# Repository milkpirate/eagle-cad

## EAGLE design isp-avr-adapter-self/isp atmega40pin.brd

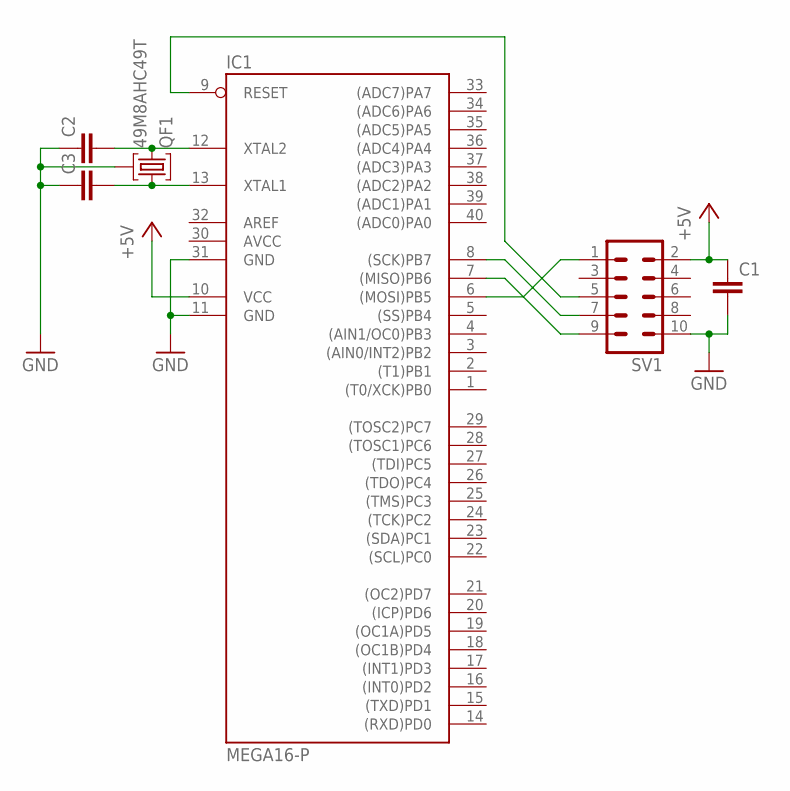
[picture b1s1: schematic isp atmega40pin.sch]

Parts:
C1, C2, C3: C-EU025-025X050; C025-025X050
IC1: MEGA16-P; DIL40
QF1: 49M8AHC49T; HC49U
SV1: ML10

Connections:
+5V: C1.1, IC1.10 (VCC), SV1.2
AVCC: IC1.30 (AVCC)
GND: C1.2, C2.1, C3.1, IC1.11 (GND), IC1.31 (GND), QF1.2, SV1.10
unnamed: IC1.6 ((MOSI)PB5), SV1.1
unnamed: C2.2, IC1.12 (XTAL2), QF1.3
unnamed: IC1.9 (RESET), SV1.5
unnamed: IC1.8 ((SCK)PB7), SV1.7
unnamed: C3.2, IC1.13 (XTAL1), QF1.1
unnamed: IC1.7 ((MISO)PB6), SV1.9

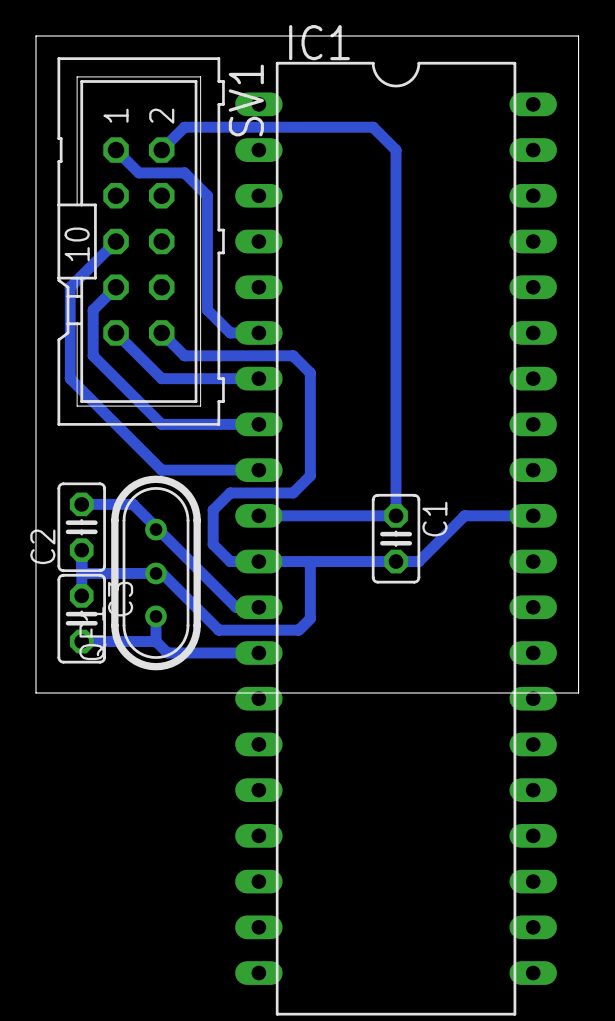
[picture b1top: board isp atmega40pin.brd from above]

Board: 2 copper layers, 30.1 x 36.5 mm, 6 parts (0 on the bottom side), 8 nets.

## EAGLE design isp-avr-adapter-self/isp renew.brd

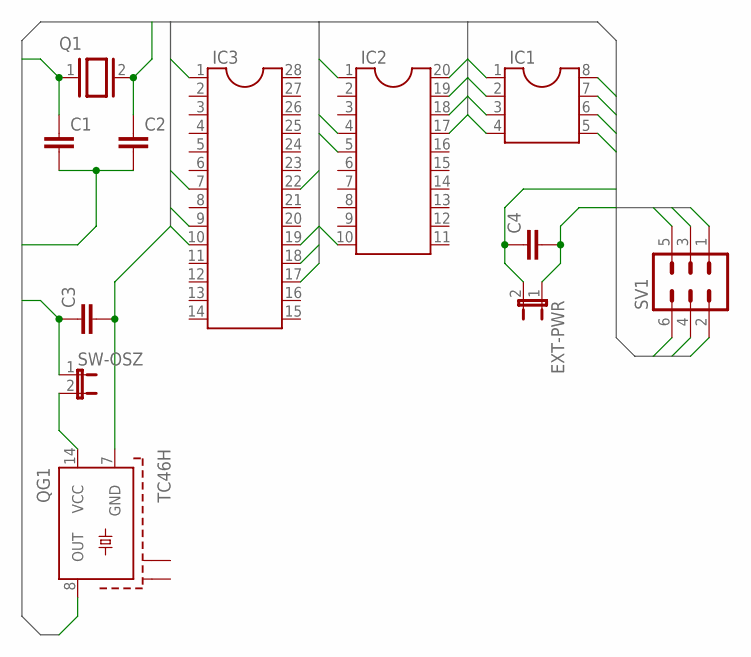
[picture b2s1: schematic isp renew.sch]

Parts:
C1, C2, C4: C-EU025-025X050; C025-025X050
C3: C-EU025-024X044; C025-024X044
EXT-PWR: JP1E; JP1
IC1: DIL8; DIL08
IC2: DIL20
IC3: DIL28-3
Q1: XTAL/S; QS
QG1: TC46H; TC46
SV1: ML6
SW-OSZ: JP1E; JP1

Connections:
GND: C1.2, C2.2, C3.2, C4.2, EXT-PWR.1, IC1.4, IC2.10, IC3.22, QG1.7 (GND), SV1.6
MISO: IC1.6, IC2.18, IC3.18, SV1.1
MOSI: IC1.5, IC2.17, IC3.17, SV1.4
unnamed: QG1.14 (VCC), SW-OSZ.2
RESET: IC1.1, IC2.1, IC3.1, SV1.5
SCK: IC1.7, IC2.19, IC3.19, SV1.3
VCC: C3.1, C4.1, EXT-PWR.2, IC1.8, IC2.20, IC3.7, SV1.2, SW-OSZ.1
XTAL1: C1.1, IC1.2, IC2.4, IC3.9, Q1.1, QG1.8 (OUT)
XTAL2: C2.1, IC1.3, IC2.5, IC3.10, Q1.2

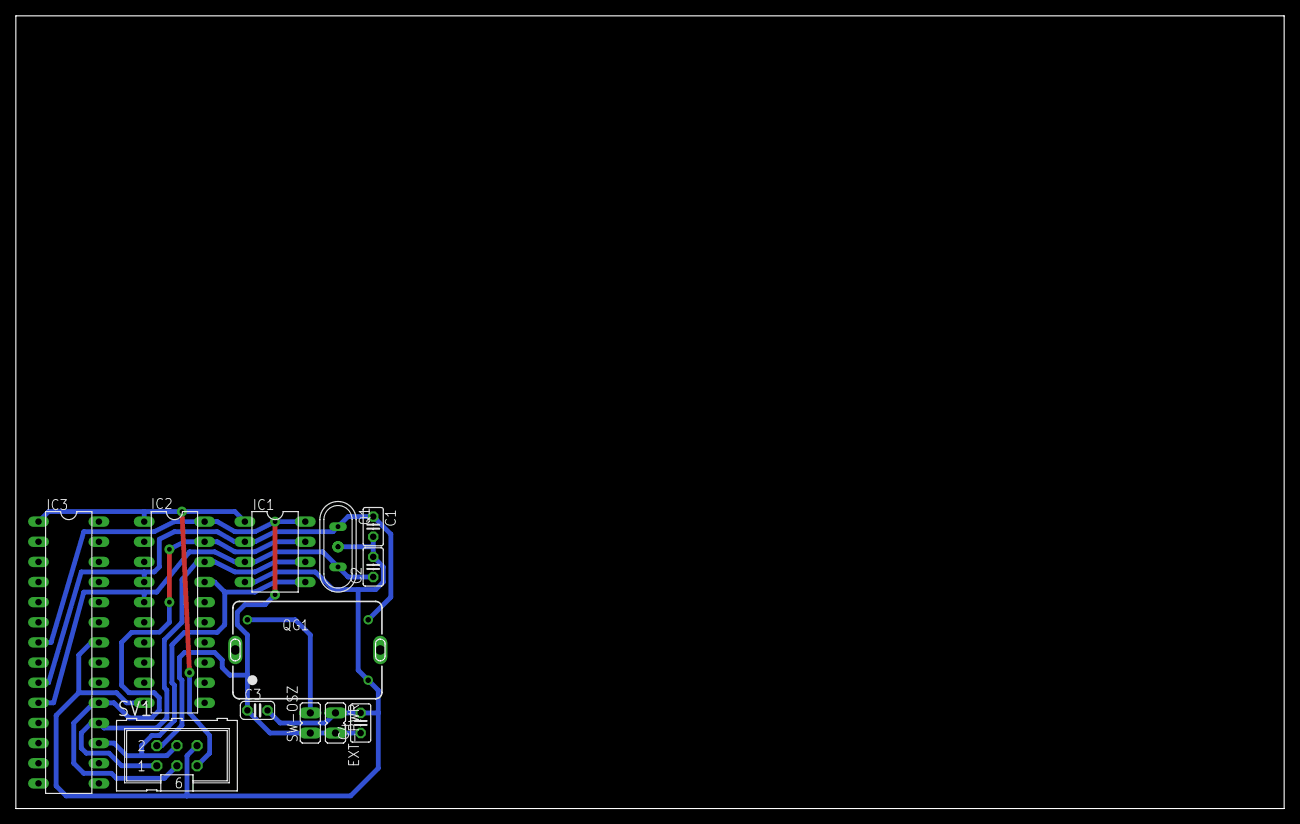
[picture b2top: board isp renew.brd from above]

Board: 2 copper layers, 160.0 x 100.0 mm, 12 parts (0 on the bottom side), 9 nets.

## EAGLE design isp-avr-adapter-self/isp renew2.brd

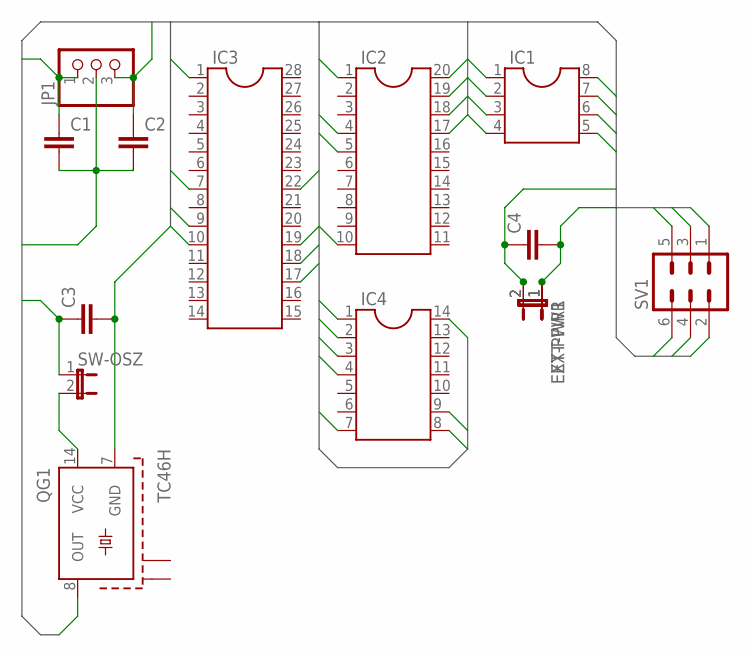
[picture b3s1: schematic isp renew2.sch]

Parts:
C1, C2, C4: C-EU025-025X050; C025-025X050
C3: C-EU025-024X044; C025-024X044
EXT-PWR, EXT-PWR1: JP1E; JP1
IC1: DIL8; DIL08
IC2: DIL20
IC3: DIL28-3
IC4: DIL14
JP1: PINHD-1X3; 1X03
QG1: TC46H; TC46
SV1: ML6
SW-OSZ: JP1E; JP1

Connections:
GND: C1.2, C2.2, C3.2, C4.2, EXT-PWR.1, EXT-PWR1.1, IC1.4, IC2.10, IC3.22, IC4.14, JP1.2, QG1.7 (GND), SV1.6
MISO: IC1.6, IC2.18, IC3.18, IC4.8, SV1.1
MOSI: IC1.5, IC2.17, IC3.17, IC4.7, SV1.4
unnamed: QG1.14 (VCC), SW-OSZ.2
RESET: IC1.1, IC2.1, IC3.1, IC4.4, SV1.5
SCK: IC1.7, IC2.19, IC3.19, IC4.9, SV1.3
VCC: C3.1, C4.1, EXT-PWR.2, EXT-PWR1.2, IC1.8, IC2.20, IC3.7, IC4.1, SV1.2, SW-OSZ.1
XTAL1: C1.1, IC1.2, IC2.4, IC3.9, IC4.2, JP1.1, QG1.8 (OUT)
XTAL2: C2.1, IC1.3, IC2.5, IC3.10, IC4.3, JP1.3

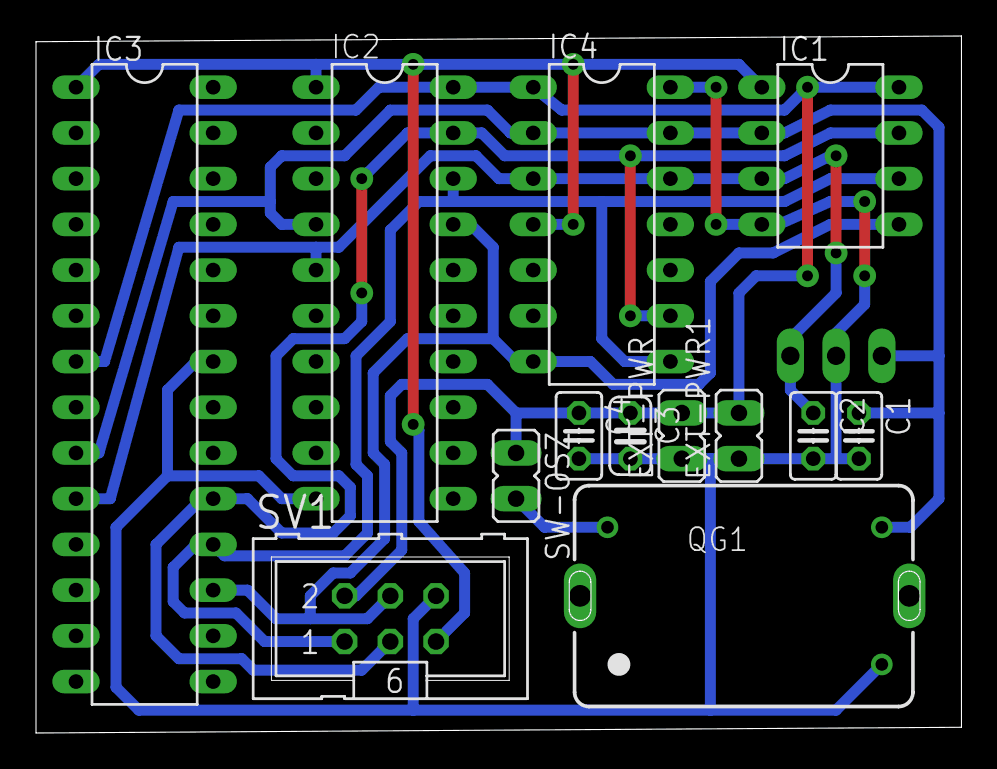
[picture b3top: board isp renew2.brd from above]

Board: 2 copper layers, 51.4 x 38.7 mm, 14 parts (1 on the bottom side), 9 nets.

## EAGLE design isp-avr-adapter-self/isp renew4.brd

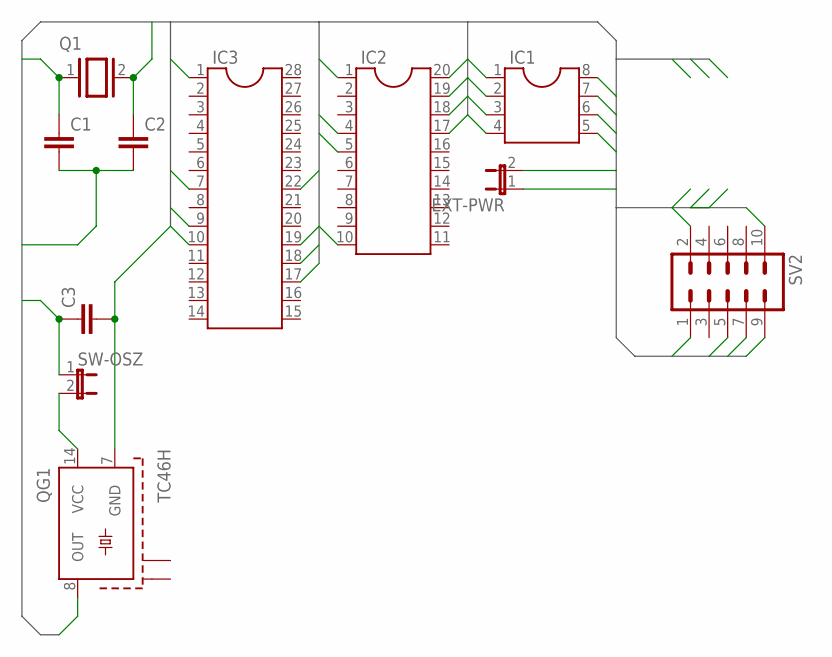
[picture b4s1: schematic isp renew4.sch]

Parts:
C1, C2: C-EU025-025X050; C025-025X050
C3: C-EU025-024X044; C025-024X044
EXT-PWR: JP1E; JP1
IC1: DIL8; DIL08
IC2: DIL20
IC3: DIL28-3
Q1: XTAL/S; QS
QG1: TC46H; TC46
SV2: ML10
SW-OSZ: JP1E; JP1

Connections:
GND: C1.2, C2.2, C3.2, EXT-PWR.1, IC1.4, IC2.10, IC3.22, QG1.7 (GND), SV2.10
MISO: IC1.6, IC2.18, IC3.18, SV2.9
MOSI: IC1.5, IC2.17, IC3.17, SV2.1
unnamed: QG1.14 (VCC), SW-OSZ.2
RESET: IC1.1, IC2.1, IC3.1, SV2.5
SCK: IC1.7, IC2.19, IC3.19, SV2.7
VCC: C3.1, EXT-PWR.2, IC1.8, IC2.20, IC3.7, SV2.2, SW-OSZ.1
XTAL1: C1.1, IC1.2, IC2.4, IC3.9, Q1.1, QG1.8 (OUT)
XTAL2: C2.1, IC1.3, IC2.5, IC3.10, Q1.2

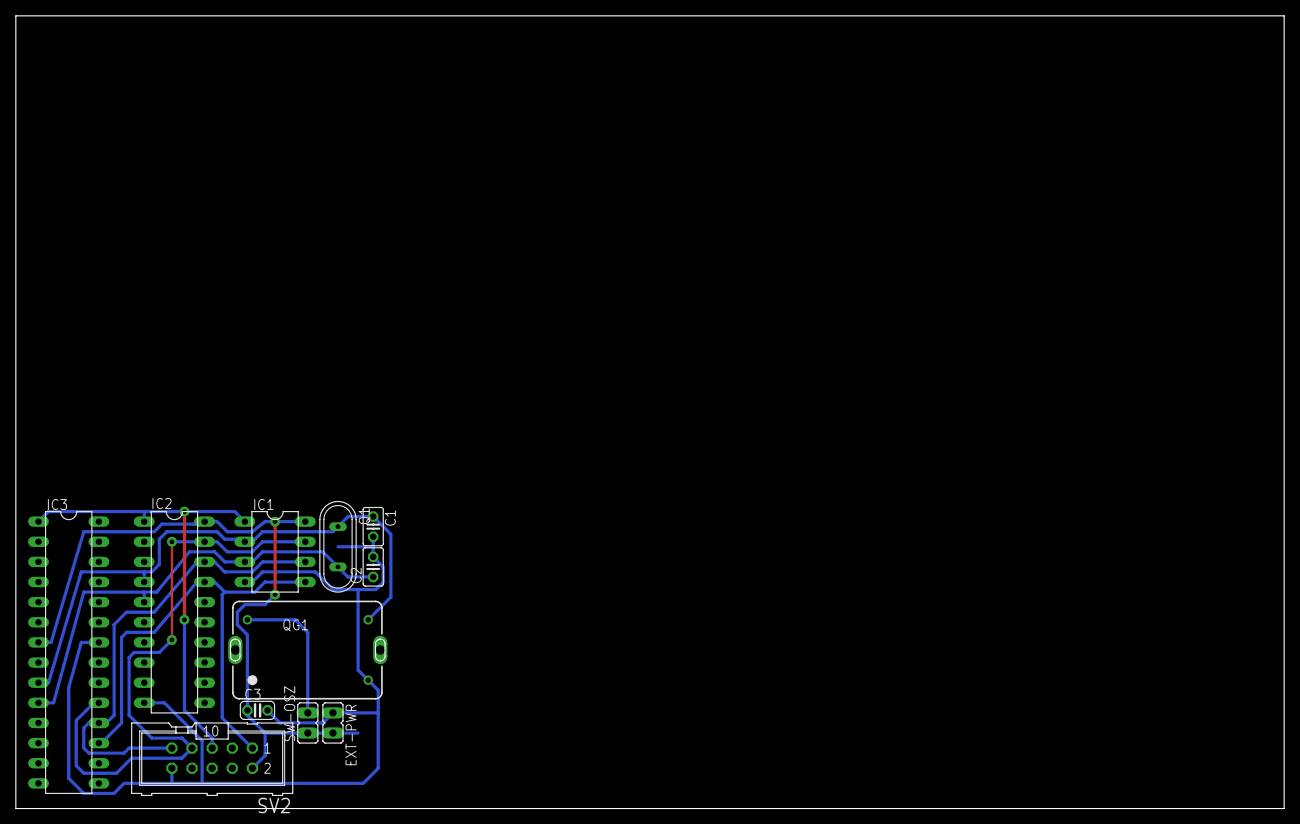
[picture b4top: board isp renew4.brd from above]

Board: 2 copper layers, 160.0 x 100.0 mm, 11 parts (0 on the bottom side), 9 nets.

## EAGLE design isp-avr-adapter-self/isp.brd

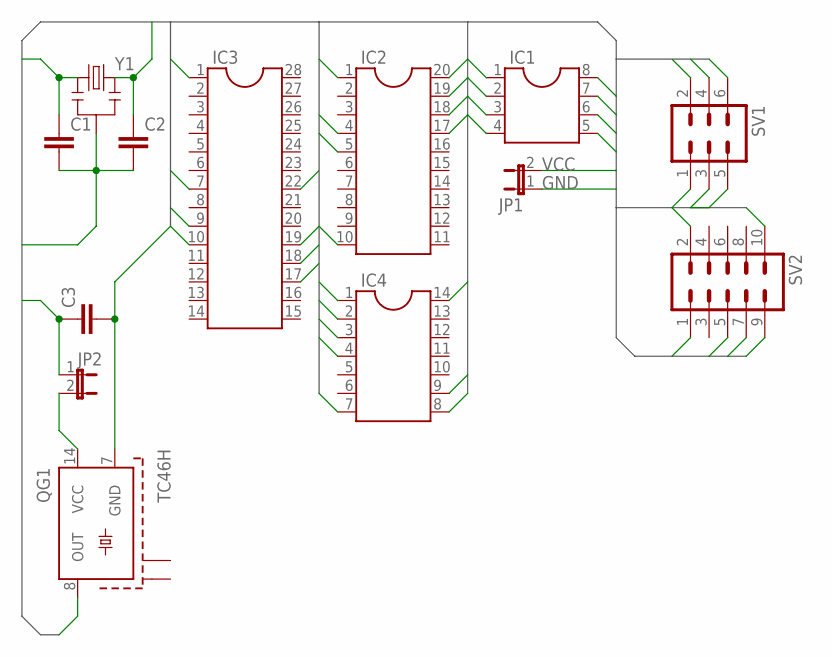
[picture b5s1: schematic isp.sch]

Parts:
C1, C2: C-EU025_050-025X075; C025_050-025X075
C3: C-EU025-024X044; C025-024X044
IC1: DIL8; DIL08
IC2: DIL20
IC3: DIL28-3
IC4: DIL14
JP1, JP2: JP1E; JP1
QG1: TC46H; TC46
SV1: ML6
SV2: ML10
Y1: RESONATORPTH; RESONATOR-PTH

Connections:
GND: C1.2, C2.2, C3.2, IC1.4, IC2.10, IC3.22, IC4.14, JP1.1, QG1.7 (GND), SV1.6, SV2.10, Y1.2
MISO: IC1.6, IC2.18, IC3.18, IC4.8, SV1.1, SV2.9
MOSI: IC1.5, IC2.17, IC3.17, IC4.7, SV1.4, SV2.1
unnamed: JP2.2, QG1.14 (VCC)
RESET: IC1.1, IC2.1, IC3.1, IC4.4, SV1.5, SV2.5
SCK: IC1.7, IC2.19, IC3.19, IC4.9, SV1.3, SV2.7
VCC: C3.1, IC1.8, IC2.20, IC3.7, IC4.1, JP1.2, JP2.1, SV1.2, SV2.2
XTAL1: C1.1, IC1.2, IC2.4, IC3.9, IC4.2, QG1.8 (OUT), Y1.1
XTAL2: C2.1, IC1.3, IC2.5, IC3.10, IC4.3, Y1.3

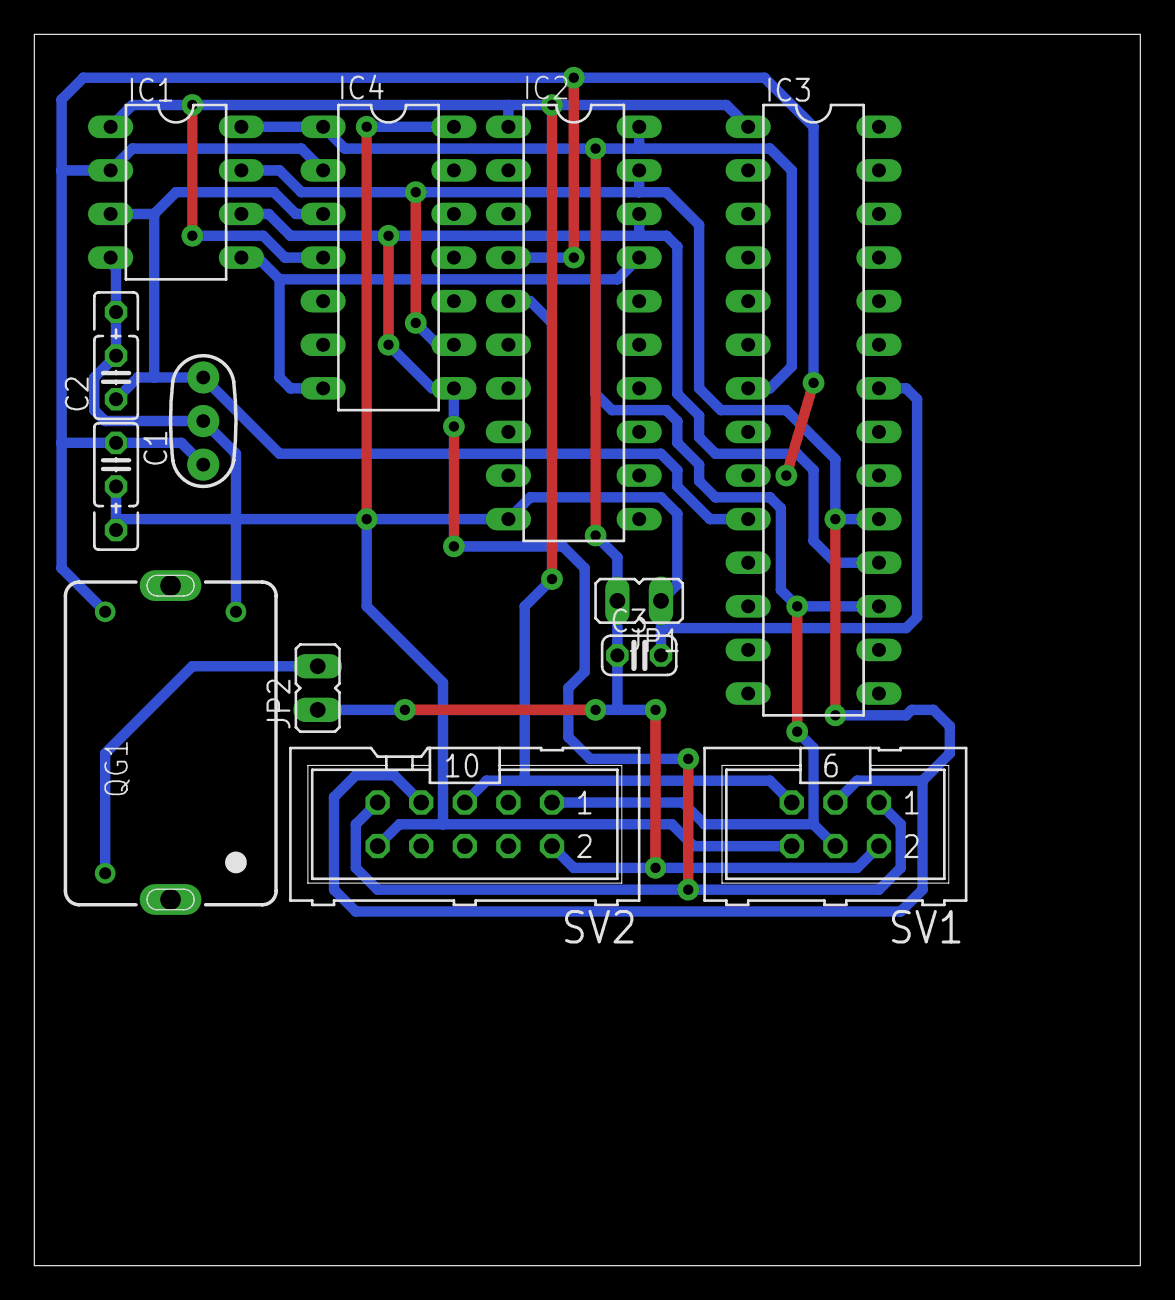
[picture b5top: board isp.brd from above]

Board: 2 copper layers, 64.4 x 71.7 mm, 13 parts (0 on the bottom side), 9 nets.

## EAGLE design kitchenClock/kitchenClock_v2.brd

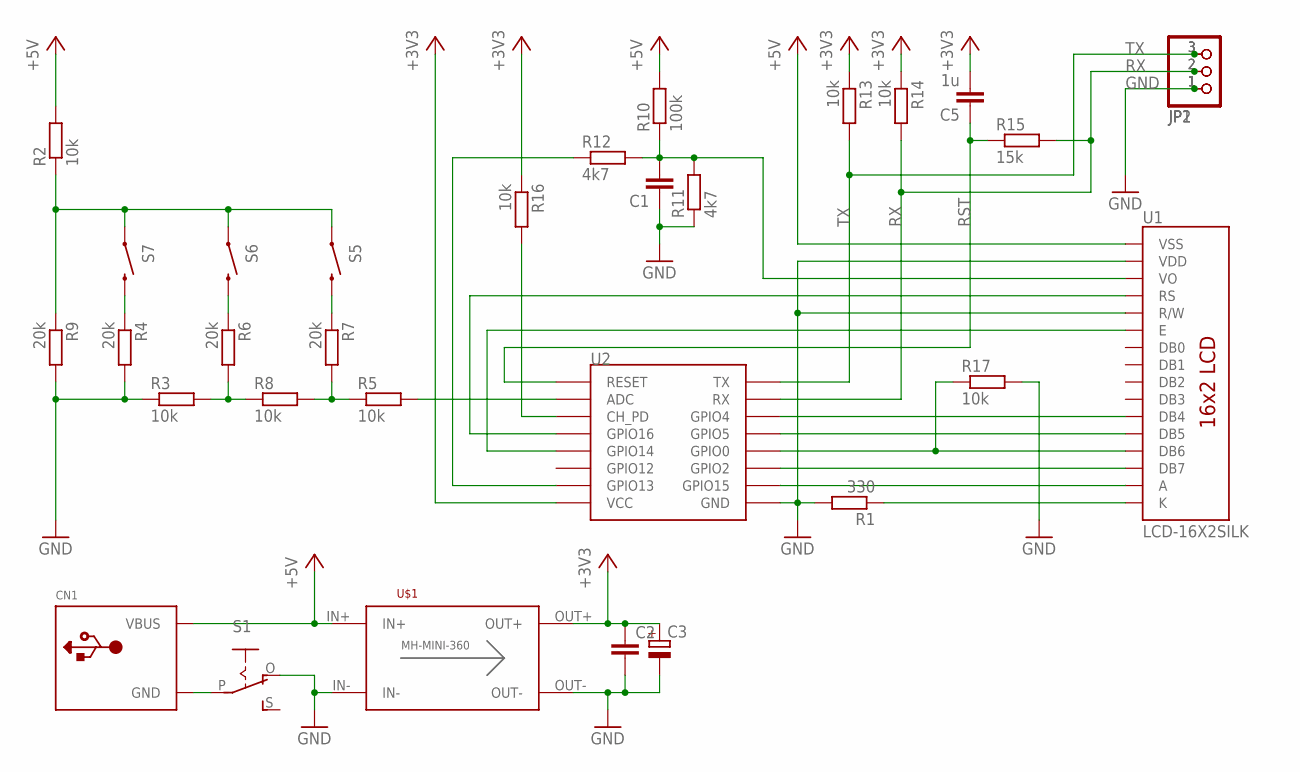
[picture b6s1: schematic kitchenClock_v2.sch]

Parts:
C1: C-EU050-025X075; C050-025X075
C2: C-EU025-025X050; C025-025X050
C3: CPOL-EUTT2D5L; TT2D5L
C5: 1u; C025-025X050
CN1: USBPWR-ONLY; USB-MINIB-THM
JP1: PINHD-1X3/90; 1X03/90
JP2: PINHD-1X3; 1X03
R1: 330; 0204/7
R2, R3, R5, R8, R13, R14, R16: 10k; 0204/7
R4, R6, R7, R9: 20k; 0204/7
R10: 100k; 0204/7
R11, R12: 4k7; 0204/7
R15: 15k; 0204/7
R17: 10k; M0805
S1: EG1218S; EG1218
S5, S6, S7: SWITCH-MOMENTARY-2SIDE_EZ; TACTILE-PTH-SIDEEZ
U1: LCD-16X2SILK; LCD-16X2
U2: ESP12EDIP; ESP-12-BREAKOUT
U$1: DC-DC_CONV_MINISTD; DC-DC_CONV_MINI

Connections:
+3V3: C2.1, C3.+, C5.2, R13.1, R14.1, R16.1, U2.P$1 (VCC), U$1.OUT+
+5V: CN1.VBUS, R2.2, R10.2, U1.1 (VSS), U$1.IN+
GND: C1.1, C2.2, C3.-, JP1.1, JP2.1, R1.2, R3.1, R4.2, R9.2, R11.1, R17.2, S1.O, U1.2 (VDD), U1.5 (R/W), U2.P$9 (GND), U$1.IN-, U$1.OUT-
unnamed: R1.1, U1.16 (K)
unnamed: R12.1, U2.P$2 (GPIO13)
unnamed: U1.4 (RS), U2.P$5 (GPIO16)
unnamed: U1.6 (E), U2.P$4 (GPIO14)
unnamed: U1.11 (DB4), U2.P$14 (GPIO4)
unnamed: U1.12 (DB5), U2.P$13 (GPIO5)
unnamed: R17.1, U1.13 (DB6), U2.P$12 (GPIO0)
unnamed: U1.14 (DB7), U2.P$11 (GPIO2)
unnamed: U1.15 (A), U2.P$10 (GPIO15)
unnamed: R5.2, U2.P$7 (ADC)
unnamed: R2.1, R9.1, S5.1, S6.1, S7.1
unnamed: CN1.GND, CN1.GND1 (GND), CN1.GND2 (GND), CN1.GND3 (GND), CN1.GND4 (GND), S1.P
unnamed: R3.2, R6.2, R8.1
unnamed: R5.1, R7.2, R8.2
unnamed: R7.1, S5.2
unnamed: R6.1, S6.2
unnamed: R4.1, S7.2
unnamed: R16.2, U2.P$6 (CH_PD)
unnamed: C1.2, R10.1, R11.2, R12.2, U1.3 (VO)
RST: C5.1, R15.1, U2.P$8 (RESET)
RX: JP1.2, JP2.2, R14.2, R15.2, U2.P$15 (RX)
TX: JP1.3, JP2.3, R13.2, U2.P$16 (TX)

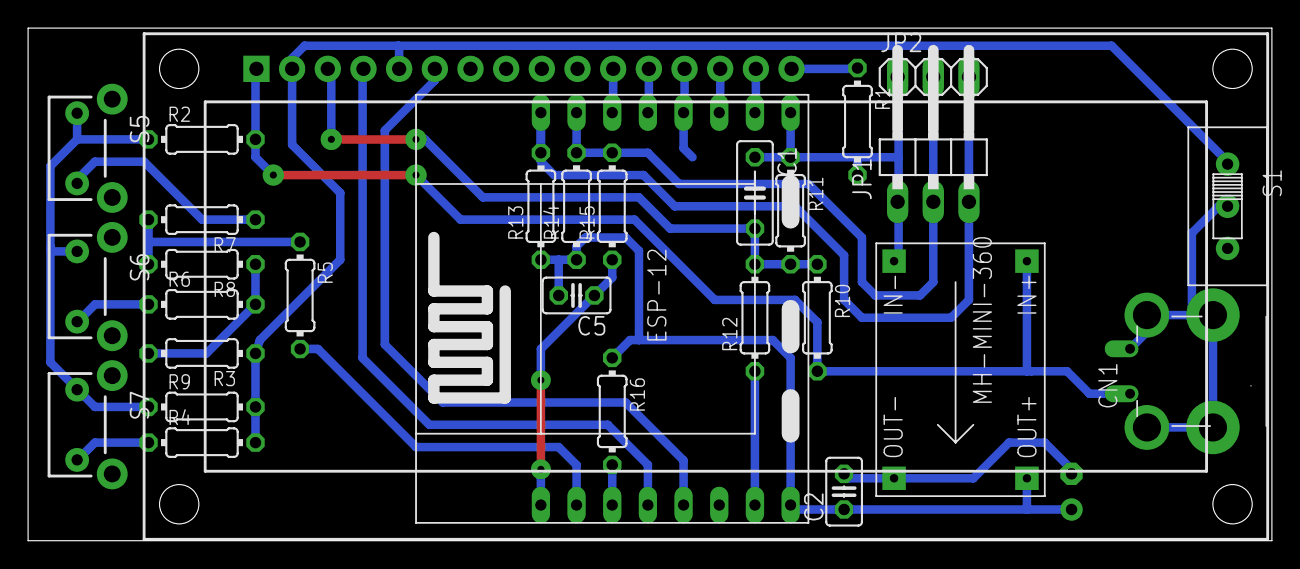
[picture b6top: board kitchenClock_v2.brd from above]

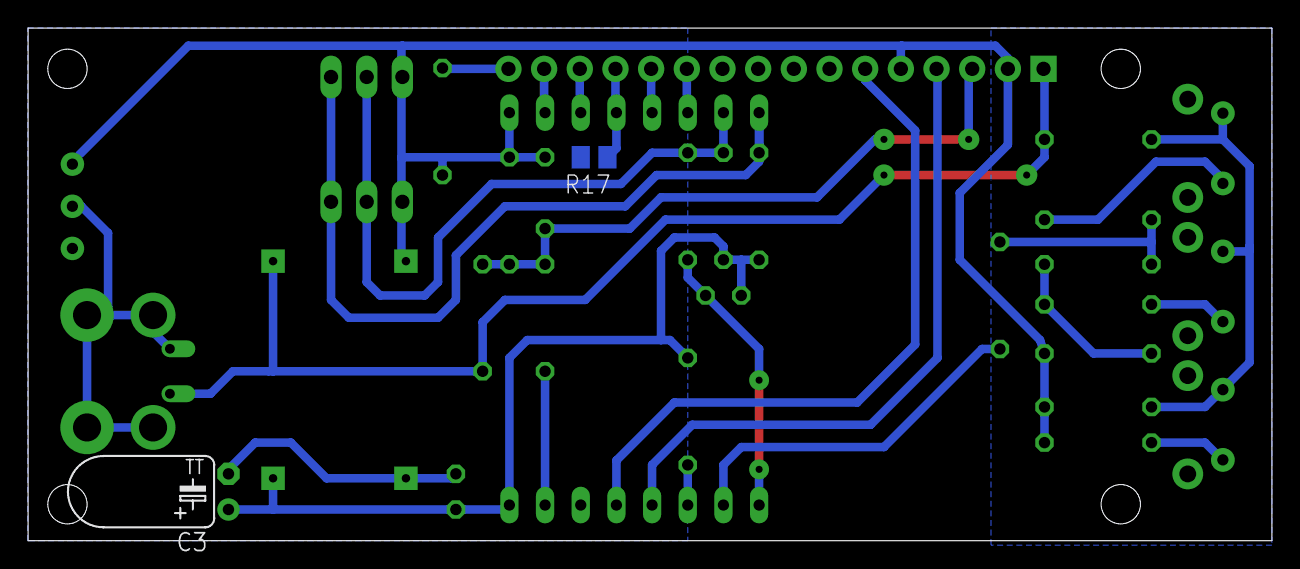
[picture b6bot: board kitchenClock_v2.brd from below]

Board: 2 copper layers, 88.6 x 36.5 mm, 31 parts (2 on the bottom side), 25 nets.

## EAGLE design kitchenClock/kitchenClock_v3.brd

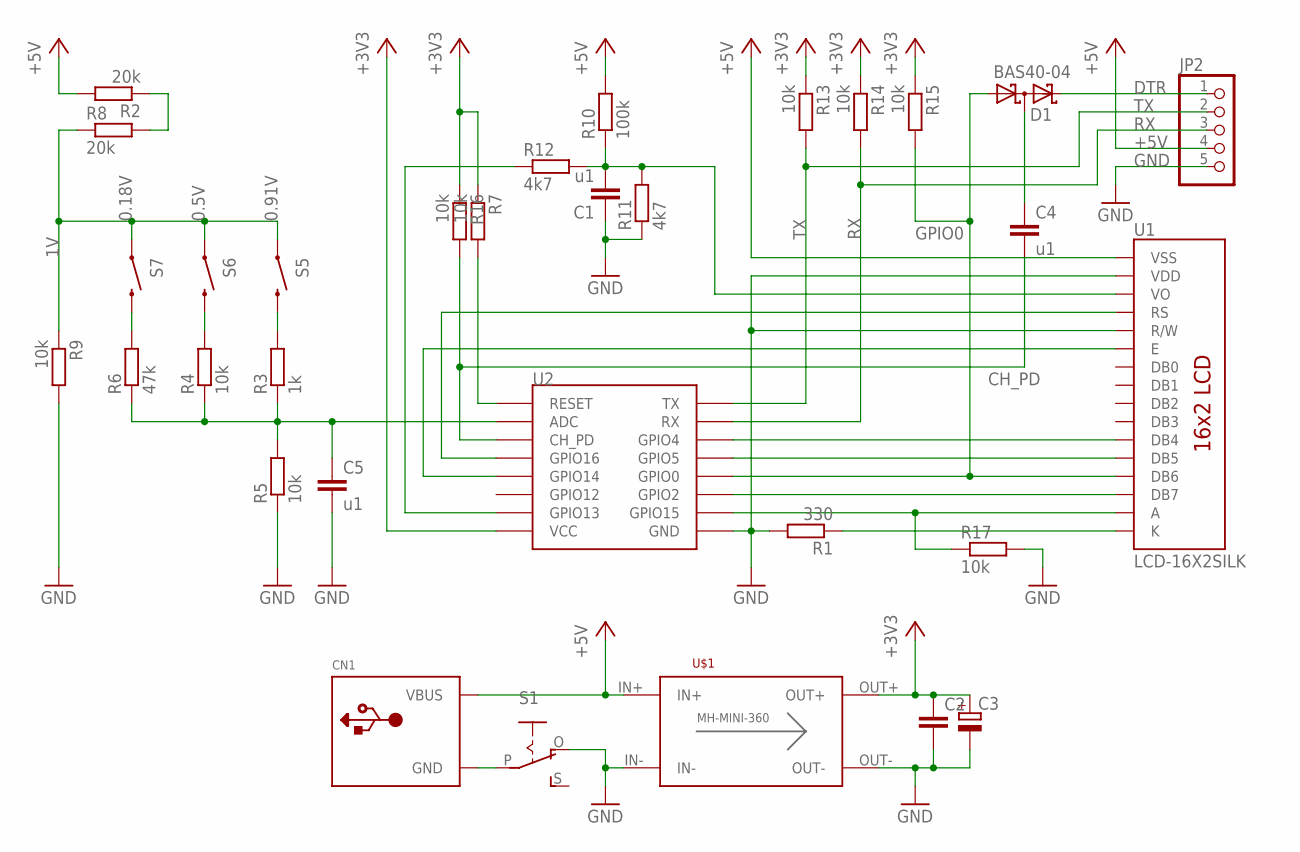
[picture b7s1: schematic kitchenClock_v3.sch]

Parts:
C1, C4: u1; C075-032X103
C2: C-EU025-025X050; C025-025X050
C3: CPOL-EUTT2D5L; TT2D5L
C5: u1; C025-025X050
CN1: USBPWR-ONLY; USB-MINIB-THM
D1: BAS40-04; SOT23
JP2: PINHD-1X5/90; 1X05/90
R1: 330; M0805
R2, R8: 20k; 0204/7
R3: 1k; 0204/7
R4, R5, R7, R9: 10k; 0204/7
R6: 47k; 0204/7
R10: 100k; M0805
R11: 4k7; 0204/7
R12: 4k7; 0207/10
R13, R14, R15: 10k; 0207/10
R16, R17: 10k; M0805
S1: EG1218S; EG1218
S5, S6, S7: SWITCH-MOMENTARY-2SIDE_EZ; TACTILE-PTH-SIDEEZ
U1: LCD-16X2SILK; LCD-16X2
U2: ESP12EDIP; ESP-12-BREAKOUT
U$1: DC-DC_CONV_MINISTD; DC-DC_CONV_MINI

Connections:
1V: R8.1, R9.1, S5.1, S6.1, S7.1
+3V3: C2.1, C3.+, R7.1, R13.1, R14.1, R15.1, R16.1, U2.P$1 (VCC), U$1.OUT+
+5V: CN1.VBUS, JP2.4, R2.2, R10.2, U1.1 (VSS), U$1.IN+
CH_PD: C4.2, R16.2, U2.P$6 (CH_PD)
DTR: D1.2 (C2), JP2.1
GND: C1.1, C2.2, C3.-, C5.2, JP2.5, R1.2, R5.1, R9.2, R11.1, R17.2, S1.O, U1.2 (VDD), U1.5 (R/W), U2.P$9 (GND), U$1.IN-, U$1.OUT-
GPIO0: D1.1 (A1), R15.2, U1.13 (DB6), U2.P$12 (GPIO0)
unnamed: R1.1, U1.16 (K)
unnamed: R12.1, U2.P$2 (GPIO13)
unnamed: U1.4 (RS), U2.P$5 (GPIO16)
unnamed: U1.6 (E), U2.P$4 (GPIO14)
unnamed: U1.11 (DB4), U2.P$14 (GPIO4)
unnamed: U1.12 (DB5), U2.P$13 (GPIO5)
unnamed: R3.2, S5.2
unnamed: U1.14 (DB7), U2.P$11 (GPIO2)
unnamed: R17.1, U1.15 (A), U2.P$10 (GPIO15)
unnamed: C5.1, R3.1, R4.1, R5.2, R6.1, U2.P$7 (ADC)
unnamed: R4.2, S6.2
unnamed: CN1.GND, CN1.GND1 (GND), CN1.GND2 (GND), CN1.GND3 (GND), CN1.GND4 (GND), S1.P
unnamed: R6.2, S7.2
unnamed: R7.2, U2.P$8 (RESET)
unnamed: R2.1, R8.2
unnamed: C4.1, D1.3 (C1A2)
unnamed: C1.2, R10.1, R11.2, R12.2, U1.3 (VO)
RX: JP2.3, R14.2, U2.P$15 (RX)
TX: JP2.2, R13.2, U2.P$16 (TX)

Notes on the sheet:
0.18V
0.5V
0.91V

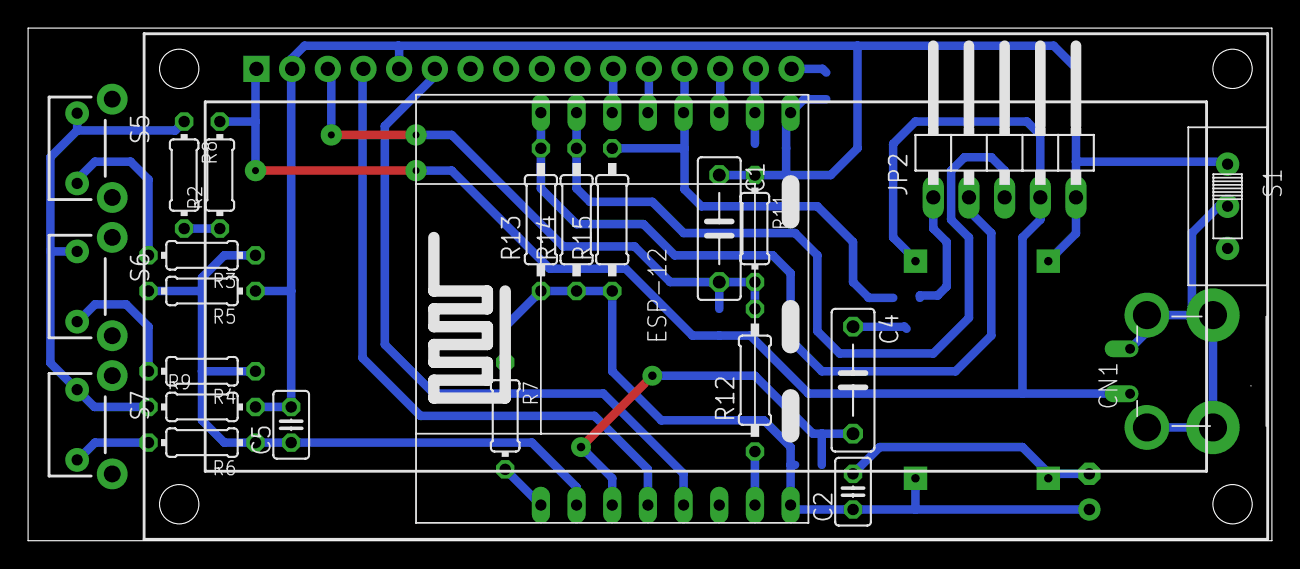
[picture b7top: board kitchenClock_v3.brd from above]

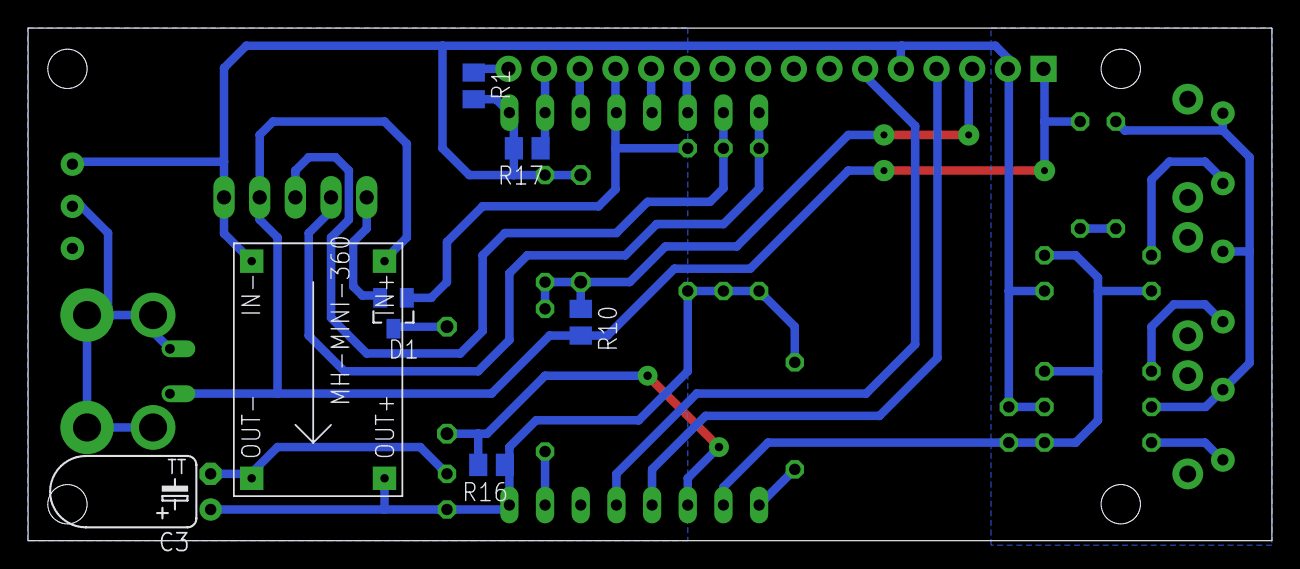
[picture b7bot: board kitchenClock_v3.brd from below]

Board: 2 copper layers, 88.6 x 36.5 mm, 32 parts (7 on the bottom side), 26 nets.

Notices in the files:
parts and their libraries:
SparkFun-FreqCtrl: Licensing: Creative Commons ShareAlike 4.0 International - https://creativecommons.org/licenses/by-sa/4.0
